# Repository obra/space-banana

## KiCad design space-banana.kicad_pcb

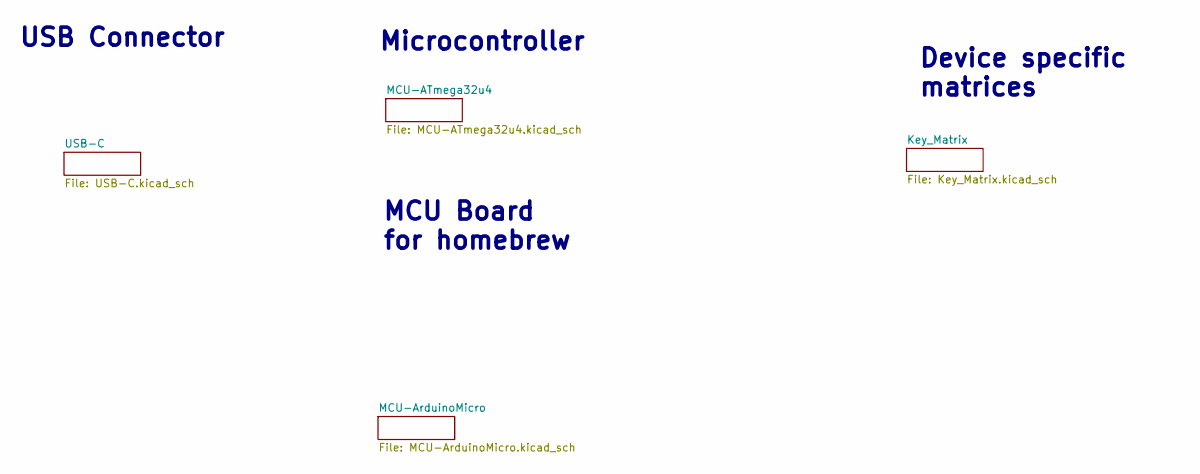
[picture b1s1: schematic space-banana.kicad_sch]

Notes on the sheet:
Microcontroller
Device specific matrices
MCU Board for homebrew
USB Connector

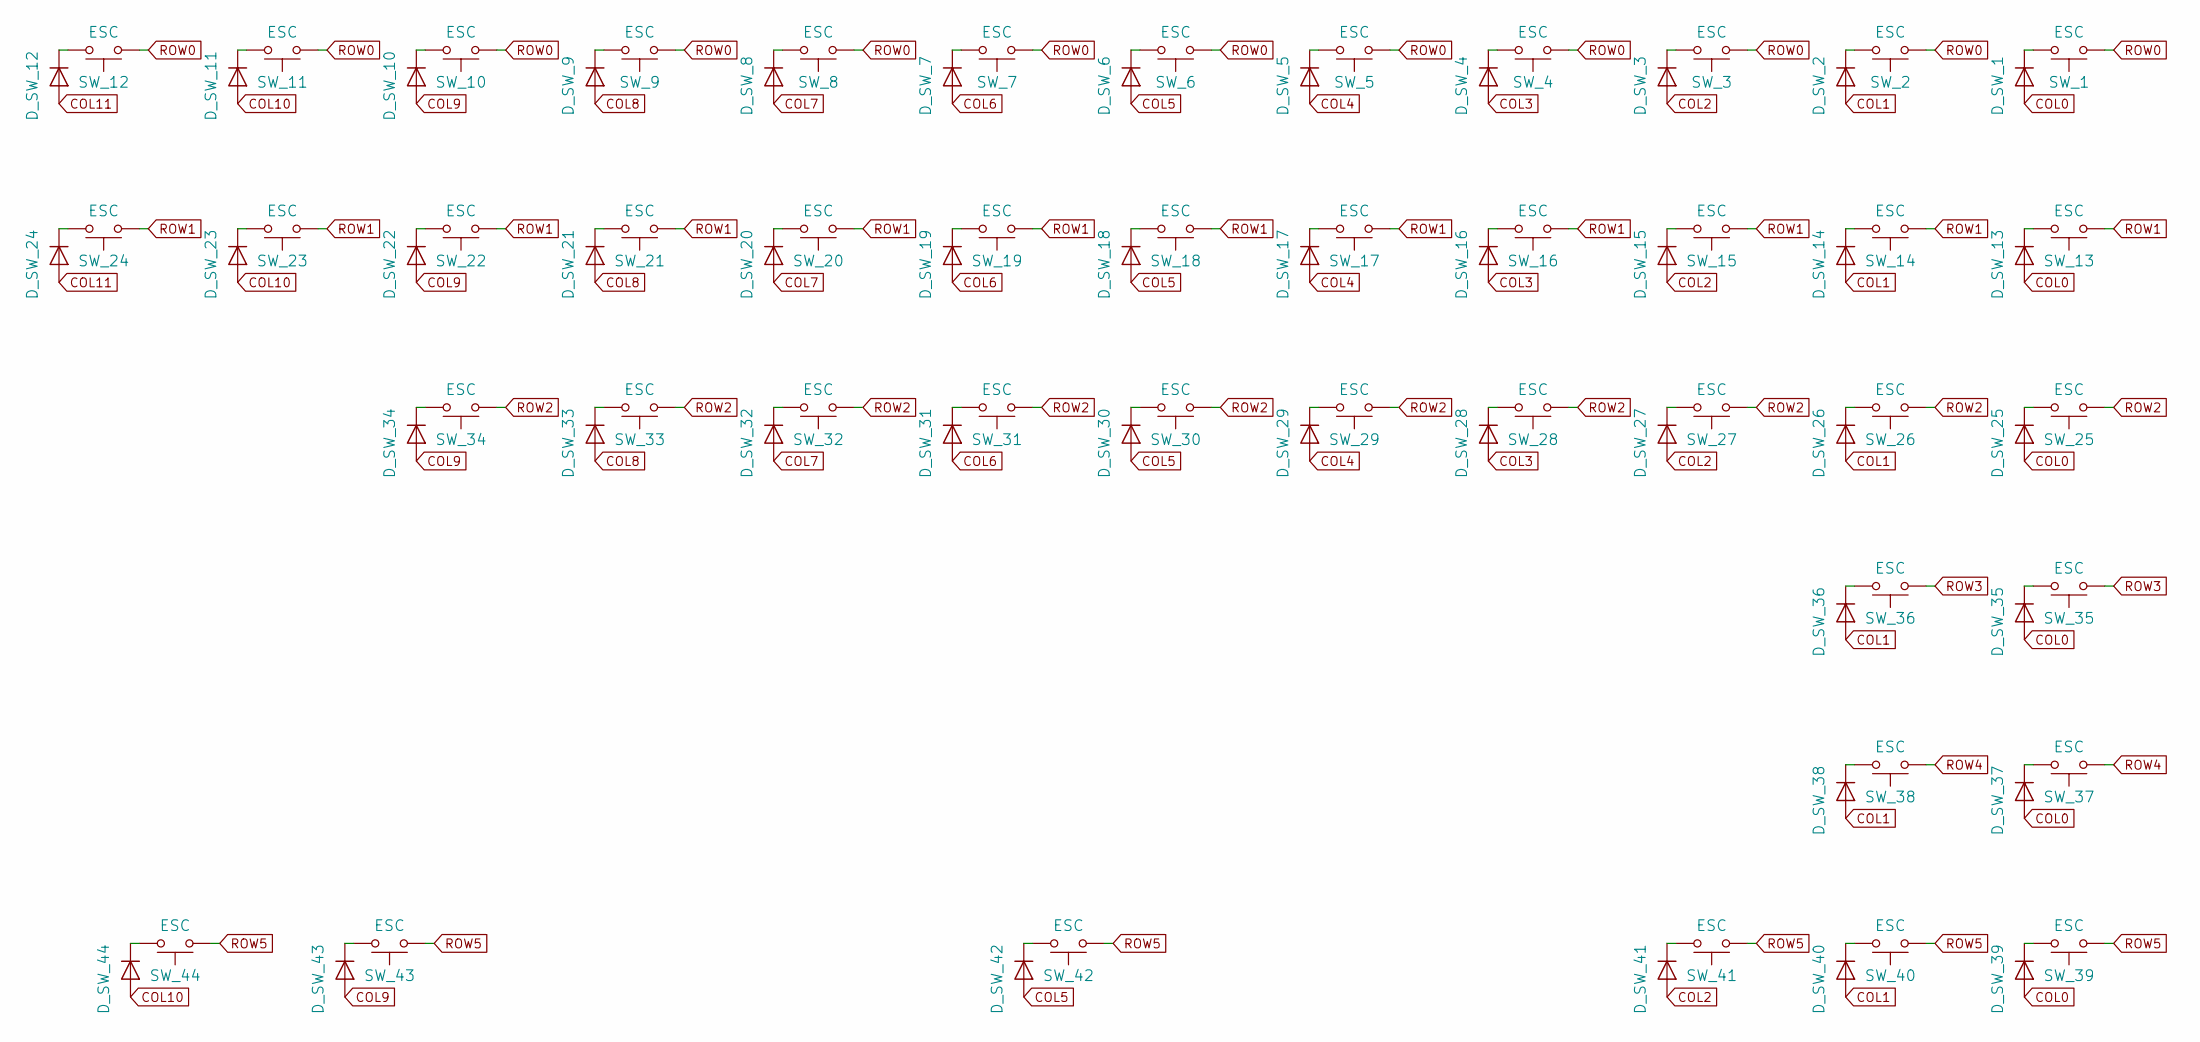
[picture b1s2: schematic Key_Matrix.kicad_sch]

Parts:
D_SW_1, D_SW_2, D_SW_3, D_SW_4, D_SW_5, D_SW_6, D_SW_7, D_SW_8, D_SW_9, D_SW_10, D_SW_11, D_SW_12, D_SW_13, D_SW_14, D_SW_15, D_SW_16, D_SW_17, D_SW_18, D_SW_19, D_SW_20, D_SW_21, D_SW_22, D_SW_23, D_SW_24, D_SW_25, D_SW_26, D_SW_27, D_SW_28, D_SW_29, D_SW_30, D_SW_31, D_SW_32, D_SW_33, D_SW_34, D_SW_35, D_SW_36, D_SW_37, D_SW_38, D_SW_39, D_SW_40, D_SW_41, D_SW_42, D_SW_43, D_SW_44: D_SOD-123
SW_1, SW_2, SW_3, SW_4, SW_5, SW_6, SW_7, SW_8, SW_9, SW_10, SW_11, SW_12, SW_13, SW_14, SW_15, SW_16, SW_17, SW_18, SW_19, SW_20, SW_21, SW_22, SW_23, SW_24, SW_25, SW_26, SW_27, SW_28, SW_29, SW_30, SW_31, SW_32, SW_33, SW_34, SW_35, SW_36, SW_37, SW_38, SW_39, SW_40, SW_41, SW_42, SW_43, SW_44: ESC; MX-KailhClip-1.00u-no-top-ring

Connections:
COL0: D_SW_1.2 (A), D_SW_13.2 (A), D_SW_25.2 (A), D_SW_35.2 (A), D_SW_37.2 (A), D_SW_39.2 (A); also elsewhere on the board
COL1: D_SW_2.2 (A), D_SW_14.2 (A), D_SW_26.2 (A), D_SW_36.2 (A), D_SW_38.2 (A), D_SW_40.2 (A); also elsewhere on the board
COL2: D_SW_3.2 (A), D_SW_15.2 (A), D_SW_27.2 (A), D_SW_41.2 (A); also elsewhere on the board
COL3: D_SW_4.2 (A), D_SW_16.2 (A), D_SW_28.2 (A); also elsewhere on the board
COL4: D_SW_5.2 (A), D_SW_17.2 (A), D_SW_29.2 (A); also elsewhere on the board
COL5: D_SW_6.2 (A), D_SW_18.2 (A), D_SW_30.2 (A), D_SW_42.2 (A); also elsewhere on the board
COL6: D_SW_7.2 (A), D_SW_19.2 (A), D_SW_31.2 (A); also elsewhere on the board
COL7: D_SW_8.2 (A), D_SW_20.2 (A), D_SW_32.2 (A); also elsewhere on the board
COL8: D_SW_9.2 (A), D_SW_21.2 (A), D_SW_33.2 (A); also elsewhere on the board
COL9: D_SW_10.2 (A), D_SW_22.2 (A), D_SW_34.2 (A), D_SW_43.2 (A); also elsewhere on the board
COL10: D_SW_11.2 (A), D_SW_23.2 (A), D_SW_44.2 (A); also elsewhere on the board
COL11: D_SW_12.2 (A), D_SW_24.2 (A); also elsewhere on the board
unnamed: D_SW_1.1 (K), SW_1.2
unnamed: D_SW_2.1 (K), SW_2.2
unnamed: D_SW_3.1 (K), SW_3.2
unnamed: D_SW_4.1 (K), SW_4.2
unnamed: D_SW_5.1 (K), SW_5.2
unnamed: D_SW_6.1 (K), SW_6.2
unnamed: D_SW_7.1 (K), SW_7.2
unnamed: D_SW_8.1 (K), SW_8.2
unnamed: D_SW_9.1 (K), SW_9.2
unnamed: D_SW_10.1 (K), SW_10.2
unnamed: D_SW_11.1 (K), SW_11.2
unnamed: D_SW_12.1 (K), SW_12.2
unnamed: D_SW_13.1 (K), SW_13.2
unnamed: D_SW_14.1 (K), SW_14.2
unnamed: D_SW_15.1 (K), SW_15.2
unnamed: D_SW_16.1 (K), SW_16.2
unnamed: D_SW_17.1 (K), SW_17.2
unnamed: D_SW_18.1 (K), SW_18.2
unnamed: D_SW_19.1 (K), SW_19.2
unnamed: D_SW_20.1 (K), SW_20.2
unnamed: D_SW_21.1 (K), SW_21.2
unnamed: D_SW_22.1 (K), SW_22.2
unnamed: D_SW_23.1 (K), SW_23.2
unnamed: D_SW_24.1 (K), SW_24.2
unnamed: D_SW_25.1 (K), SW_25.2
unnamed: D_SW_26.1 (K), SW_26.2
unnamed: D_SW_27.1 (K), SW_27.2
unnamed: D_SW_28.1 (K), SW_28.2
unnamed: D_SW_29.1 (K), SW_29.2
unnamed: D_SW_30.1 (K), SW_30.2
unnamed: D_SW_31.1 (K), SW_31.2
unnamed: D_SW_32.1 (K), SW_32.2
unnamed: D_SW_33.1 (K), SW_33.2
unnamed: D_SW_34.1 (K), SW_34.2
unnamed: D_SW_35.1 (K), SW_35.2
unnamed: D_SW_36.1 (K), SW_36.2
unnamed: D_SW_37.1 (K), SW_37.2
unnamed: D_SW_38.1 (K), SW_38.2
unnamed: D_SW_39.1 (K), SW_39.2
unnamed: D_SW_40.1 (K), SW_40.2
unnamed: D_SW_41.1 (K), SW_41.2
unnamed: D_SW_42.1 (K), SW_42.2
unnamed: D_SW_43.1 (K), SW_43.2
unnamed: D_SW_44.1 (K), SW_44.2
ROW0: SW_1.1, SW_2.1, SW_3.1, SW_4.1, SW_5.1, SW_6.1, SW_7.1, SW_8.1, SW_9.1, SW_10.1, SW_11.1, SW_12.1; also elsewhere on the board
ROW1: SW_13.1, SW_14.1, SW_15.1, SW_16.1, SW_17.1, SW_18.1, SW_19.1, SW_20.1, SW_21.1, SW_22.1, SW_23.1, SW_24.1; also elsewhere on the board
ROW2: SW_25.1, SW_26.1, SW_27.1, SW_28.1, SW_29.1, SW_30.1, SW_31.1, SW_32.1, SW_33.1, SW_34.1; also elsewhere on the board
ROW3: SW_35.1, SW_36.1; also elsewhere on the board
ROW4: SW_37.1, SW_38.1; also elsewhere on the board
ROW5: SW_39.1, SW_40.1, SW_41.1, SW_42.1, SW_43.1, SW_44.1

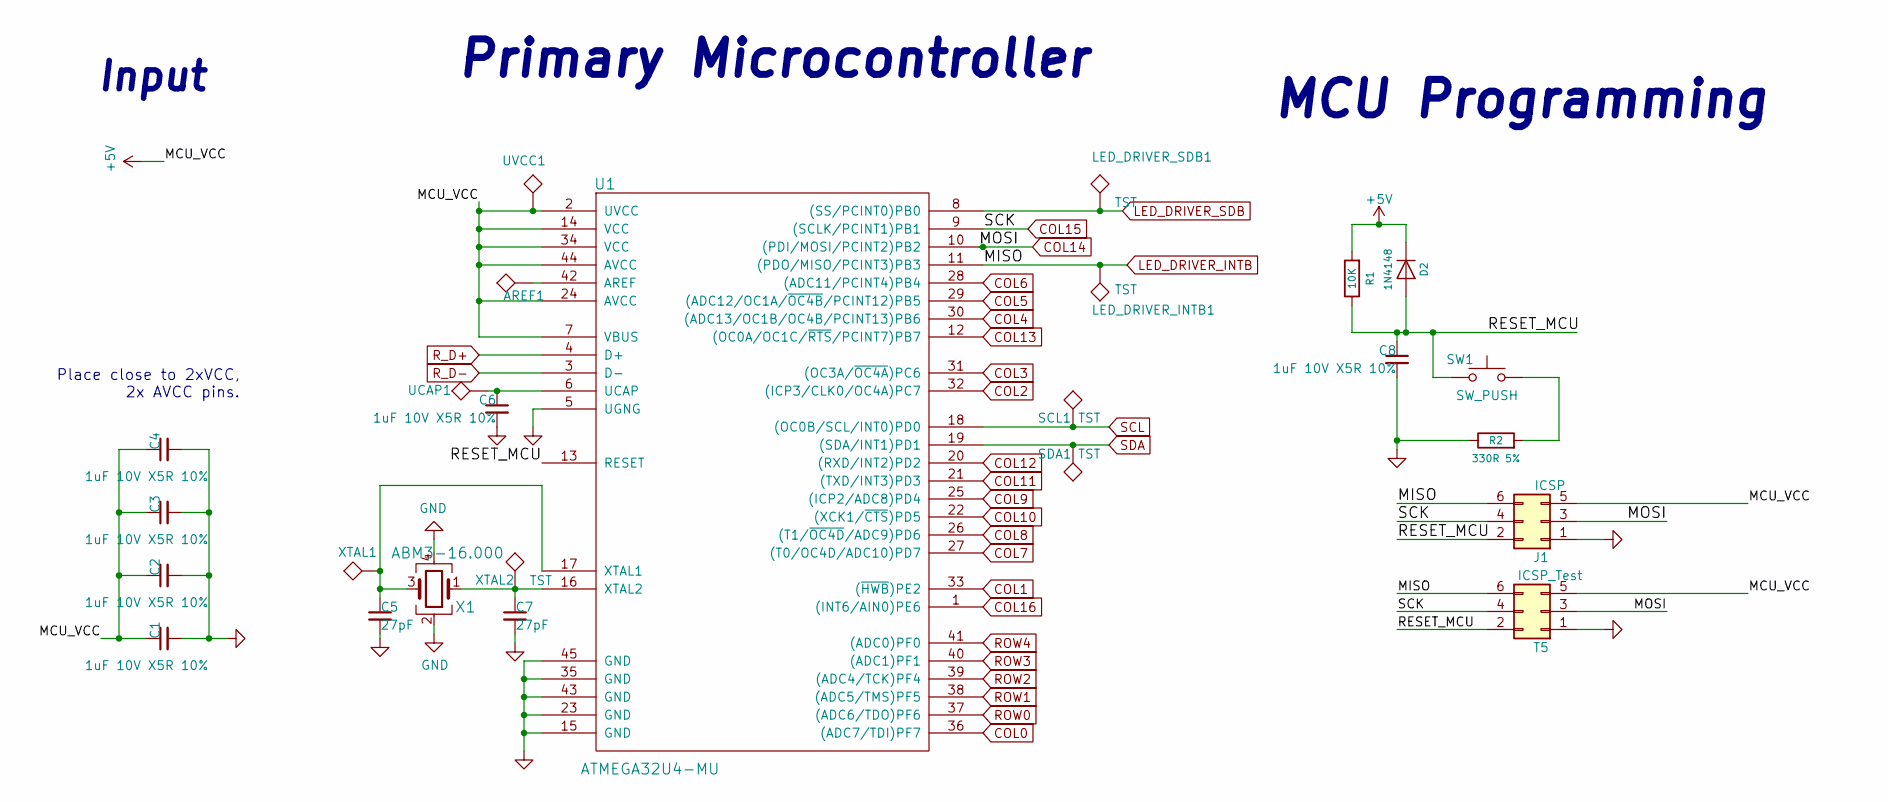
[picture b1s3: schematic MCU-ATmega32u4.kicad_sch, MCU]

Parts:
AREF1: TST; TestPoint_Pad_D1.5mm
C1, C2, C3, C4, C6, C8: 1uF 10V X5R 10%; C_0603_1608Metric; MPN CC0603KRX5R6BB105; DigiKey 311-1443-2-ND
C5, C7: 27pF; C_0603_1608Metric; MPN CC0603JRNPO9BN270; DigiKey 311-1063-1-ND
D2: 1N4148; D_SOD-123; MPN 1N4148W-7-F; DigiKey 1N4148W-FDITR-ND
J1: ICSP; Model_01_ICSP_cutout_pins; MPN M20-8760342; DigiKey 952-1922-ND
LED_DRIVER_INTB1: TST; TestPoint_Pad_D1.5mm
LED_DRIVER_SDB1: TST; TestPoint_Pad_D1.5mm
R1: 10K; R_0603_1608Metric; MPN RR0816P-103-D; DigiKey RR08P10.0KDTR-ND
R2: 330R 5%; R_0603_1608Metric; MPN 311-330GRTR-ND; DigiKey 311-330GRTR-ND
SCL1: TST; TestPoint_Pad_D1.5mm
SDA1: TST; TestPoint_Pad_D1.5mm
SW1: SW_PUSH; SW_SPST_TL3342; MPN TL3342F160QG/TR; DigiKey EG2531TR-ND
T5: ICSP_Test; Six_Pin_Test_Point
U1: ATMEGA32U4-MU; TQFP-44_10x10mm_Pitch0.8mm-Plus-QFN_44_7x7mm_Pitch_0.5mm; MPN ATMEGA32U4-MU; DigiKey ATMEGA32U4-MU-ND
UCAP1: TST; TestPoint_Pad_D1.5mm
UVCC1: TST; TestPoint_Pad_D1.5mm
X1: ABM3-16.000; ABM3_Crystal_Oscillator; MPN X1E000021069600; DigiKey TSX-322516.0000MF20G-C-ND
XTAL1, XTAL2: TST; TestPoint_Pad_D1.5mm

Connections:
+5V: C1.1, C2.1, C3.1, C4.1, D2.1 (K), J1.5, R1.2, T5.5, U1.2 (UVCC), U1.7 (VBUS), U1.14 (VCC), U1.24 (AVCC), U1.34 (VCC), U1.44 (AVCC), UVCC1.1; also elsewhere on the board
/MCU-ATmega32u4/RESET_MCU: C8.1, D2.2 (A), J1.2, R1.1, SW1.2, T5.2, U1.13 (RESET)
COL0: U1.36 ((ADC7/TDI)PF7); also elsewhere on the board
COL1: U1.33 ((~HWB)PE2); also elsewhere on the board
COL2: U1.32 ((ICP3/CLK0/OC4A)PC7); also elsewhere on the board
COL3: U1.31 ((OC3A/~OC4A)PC6); also elsewhere on the board
COL4: U1.30 ((ADC13/OC1B/OC4B/PCINT13)PB6); also elsewhere on the board
COL5: U1.29 ((ADC12/OC1A/~OC4B/PCINT12)PB5); also elsewhere on the board
COL6: U1.28 ((ADC11/PCINT4)PB4); also elsewhere on the board
COL7: U1.27 ((T0/OC4D/ADC10)PD7); also elsewhere on the board
COL8: U1.26 ((T1/~OC4D/ADC9)PD6); also elsewhere on the board
COL9: U1.25 ((ICP2/ADC8)PD4); also elsewhere on the board
COL10: U1.22 ((XCK1/~CTS)PD5); also elsewhere on the board
COL11: U1.21 ((TXD/INT3)PD3); also elsewhere on the board
COL12: U1.20 ((RXD/INT2)PD2); also elsewhere on the board
COL13: U1.12 ((OC0A/OC1C/~RTS/PCINT7)PB7); also elsewhere on the board
COL14: J1.3, T5.3, U1.10 ((PDI/MOSI/PCINT2)PB2); also elsewhere on the board
COL15: J1.4, T5.4, U1.9 ((SCLK/PCINT1)PB1); also elsewhere on the board
COL16: U1.1 ((INT6/AIN0)PE6)
LED_DRIVER_INTB: J1.6, LED_DRIVER_INTB1.1, T5.6, U1.11 ((PDO/MISO/PCINT3)PB3)
LED_DRIVER_SDB: LED_DRIVER_SDB1.1, U1.8 ((SS/PCINT0)PB0)
unnamed: AREF1.1, U1.42 (AREF)
unnamed: C5.1, U1.17 (XTAL1), X1.3, XTAL1.1
unnamed: C6.1, U1.6 (UCAP), UCAP1.1
unnamed: C7.1, U1.16 (XTAL2), X1.1, XTAL2.1
unnamed: R2.2, SW1.1
ROW0: U1.37 ((ADC6/TDO)PF6); also elsewhere on the board
ROW1: U1.38 ((ADC5/TMS)PF5); also elsewhere on the board
ROW2: U1.39 ((ADC4/TCK)PF4); also elsewhere on the board
ROW3: U1.40 ((ADC1)PF1); also elsewhere on the board
ROW4: U1.41 ((ADC0)PF0); also elsewhere on the board
R_D+: U1.4 (D+); also elsewhere on the board
R_D-: U1.3 (D-); also elsewhere on the board
SCL: SCL1.1, U1.18 ((OC0B/SCL/INT0)PD0)
SDA: SDA1.1, U1.19 ((SDA/INT1)PD1)

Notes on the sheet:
Primary Microcontroller
Input
Place close to 2xVCC, 2x AVCC pins.
MCU Programming

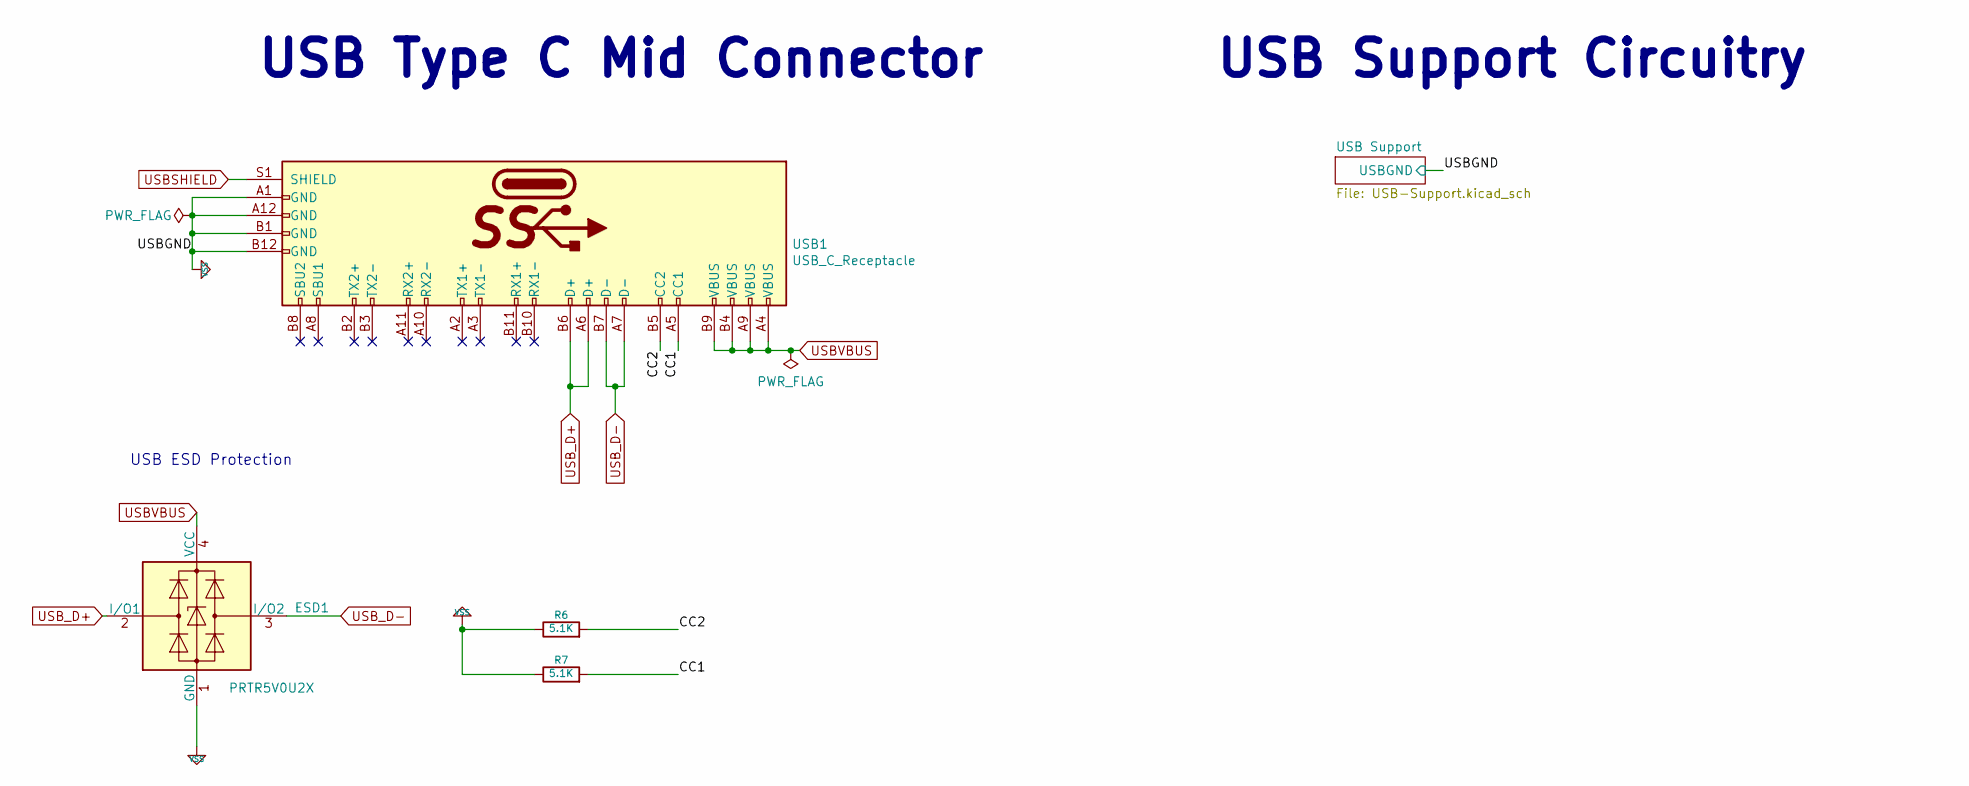
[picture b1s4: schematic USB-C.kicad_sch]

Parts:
ESD1: PRTR5V0U2X; MPN PRTR5V0U2X; DigiKey 1727-3884-2-ND
R6: 5.1K; R_0603_1608Metric; MPN RR0816P-512-D; DigiKey RR08P5.1KDTR-ND
R7: 5.1K; R_0603_1608Metric; MPN RT0603BRD075K1L; DigiKey YAG1696TR-ND
USB1: USB_C_Receptacle; USB-TYPE-C-MIDMOUNT; MPN DX07B024JJ2R1500

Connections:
/USB-C/CC1: R7.2, USB1.A5 (CC1)
/USB-C/CC2: R6.2, USB1.B5 (CC2)
USBSHIELD: USB1.S1 (SHIELD); also elsewhere on the board
USBVBUS: ESD1.4 (VCC), USB1.A4 (VBUS), USB1.A9 (VBUS), USB1.B4 (VBUS), USB1.B9 (VBUS); also elsewhere on the board
USB_D+: ESD1.2 (I/O1), USB1.A6 (D+), USB1.B6 (D+); also elsewhere on the board
USB_D-: ESD1.3 (I/O2), USB1.A7 (D-), USB1.B7 (D-); also elsewhere on the board

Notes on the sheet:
USB ESD Protection
USB Type C Mid Connector
USB Support Circuitry

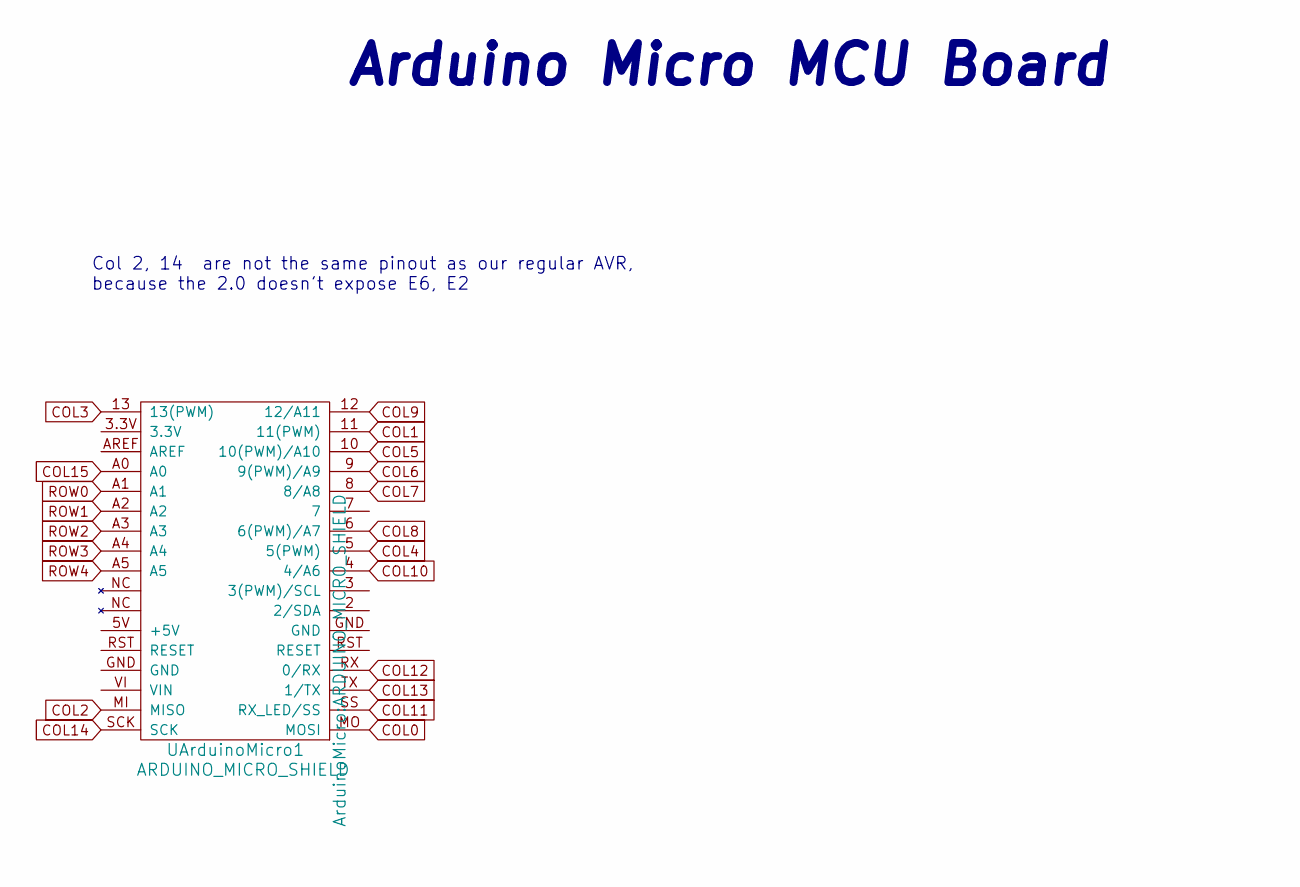
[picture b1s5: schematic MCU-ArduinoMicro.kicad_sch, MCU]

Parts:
UArduinoMicro1: ARDUINO_MICRO_SHIELD

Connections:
COL0: UArduinoMicro1.MO (MOSI); also elsewhere on the board
COL1: UArduinoMicro1.11 (11(PWM)); also elsewhere on the board
COL2: UArduinoMicro1.MI (MISO); also elsewhere on the board
COL3: UArduinoMicro1.13 (13(PWM)); also elsewhere on the board
COL4: UArduinoMicro1.5 (5(PWM)); also elsewhere on the board
COL5: UArduinoMicro1.10 (10(PWM)/A10); also elsewhere on the board
COL6: UArduinoMicro1.9 (9(PWM)/A9); also elsewhere on the board
COL7: UArduinoMicro1.8 (8/A8); also elsewhere on the board
COL8: UArduinoMicro1.6 (6(PWM)/A7); also elsewhere on the board
COL9: UArduinoMicro1.12 (12/A11); also elsewhere on the board
COL10: UArduinoMicro1.4 (4/A6); also elsewhere on the board
COL11: UArduinoMicro1.SS (RX_LED/SS); also elsewhere on the board
COL12: UArduinoMicro1.RX (0/RX); also elsewhere on the board
COL13: UArduinoMicro1.TX (1/TX); also elsewhere on the board
COL14: UArduinoMicro1.SCK; also elsewhere on the board
COL15: UArduinoMicro1.A0; also elsewhere on the board
ROW0: UArduinoMicro1.A1; also elsewhere on the board
ROW1: UArduinoMicro1.A2; also elsewhere on the board
ROW2: UArduinoMicro1.A3; also elsewhere on the board
ROW3: UArduinoMicro1.A4; also elsewhere on the board
ROW4: UArduinoMicro1.A5; also elsewhere on the board

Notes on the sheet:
Col 2, 14 are not the same pinout as our regular AVR, because the 2.0 doesn't expose E6, E2
Arduino Micro MCU Board

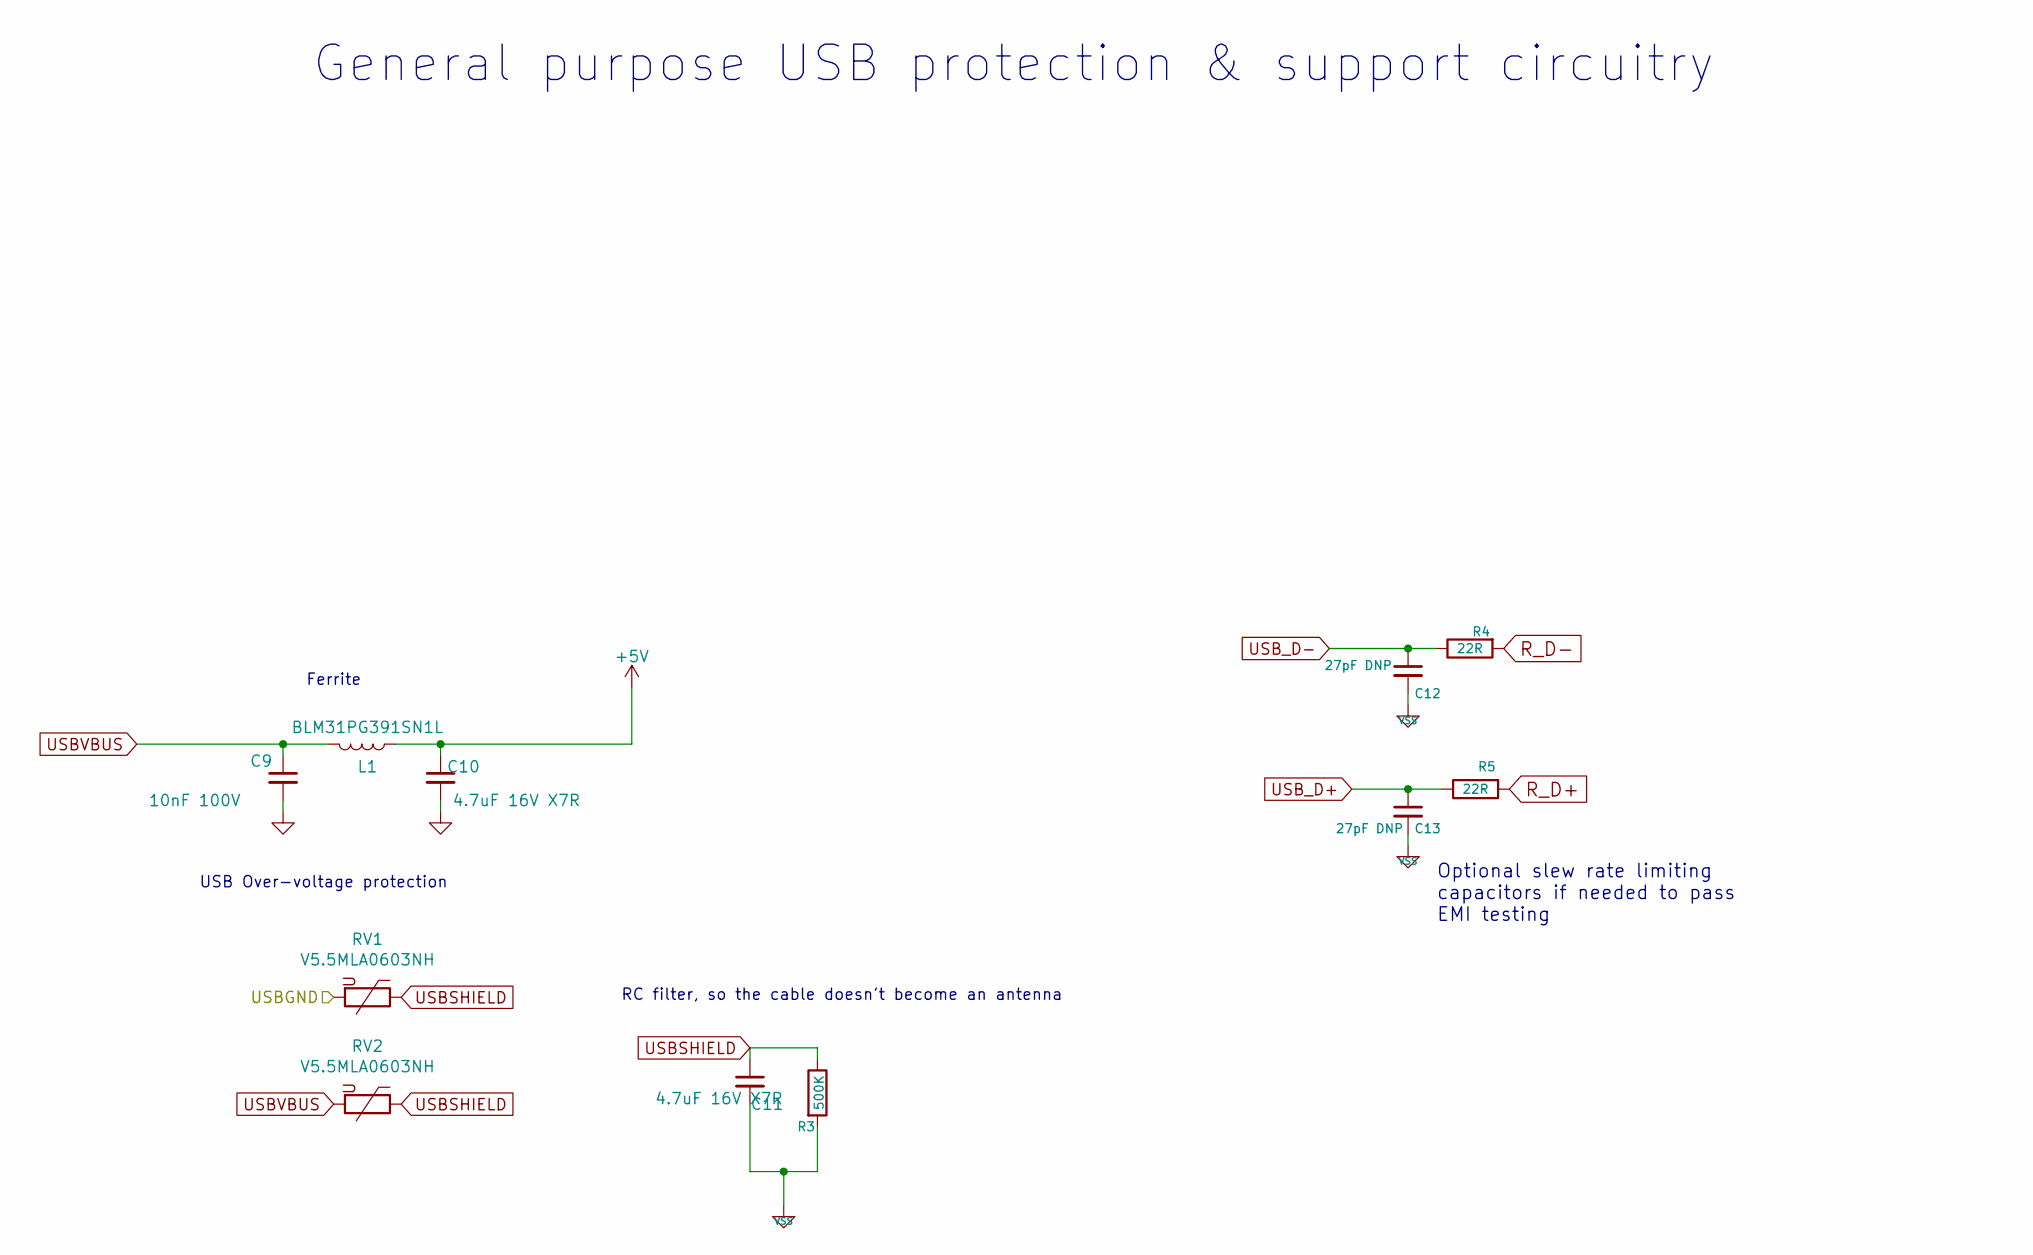
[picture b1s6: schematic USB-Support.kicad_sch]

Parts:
C9: 10nF 100V; C_0805_2012Metric; MPN CC0805KKX7R7BB475; DigiKey 311-1883-2-ND
C10: 4.7uF 16V X7R; C_0805_2012Metric; MPN CC0805KKX7R7BB475; DigiKey 311-1883-2-ND
C11: 4.7uF 16V X7R; C_0805_2012Metric; MPN CC0805KRX7R0BB103; DigiKey 311-1475-1-ND
C12, C13: 27pF DNP; C_0603_1608Metric; MPN CC0603JRNPO9BN270; DigiKey 311-1063-1-ND
L1: BLM31PG391SN1L; R_1206_3216Metric; MPN BLM31PG391SN1L; DigiKey 490-5229-2-ND
R3: 500K; R_0603_1608Metric; MPN RC0603FR-07499KL; DigiKey 311-499KHRTR-ND
R4, R5: 22R; R_0603_1608Metric; MPN RC0603FR-0722RL; DigiKey 311-22.0HRTR-ND
RV1, RV2: V5.5MLA0603NH; R_0603_1608Metric; MPN V5.5MLA0603NH; DigiKey F3363CT-ND

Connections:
+5V: C10.1, L1.1; also elsewhere on the board
R_D+: R5.2; also elsewhere on the board
R_D-: R4.2; also elsewhere on the board
USBSHIELD: C11.1, R3.1, RV1.1, RV2.1; also elsewhere on the board
USBVBUS: C9.1, L1.2, RV2.2; also elsewhere on the board
USB_D+: C13.1, R5.1; also elsewhere on the board
USB_D-: C12.1, R4.1; also elsewhere on the board

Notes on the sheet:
USB Over-voltage protection
General purpose USB protection & support circuitry
RC filter, so the cable doesn't become an antenna
Ferrite
Optional slew rate limiting capacitors if needed to pass EMI testing

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
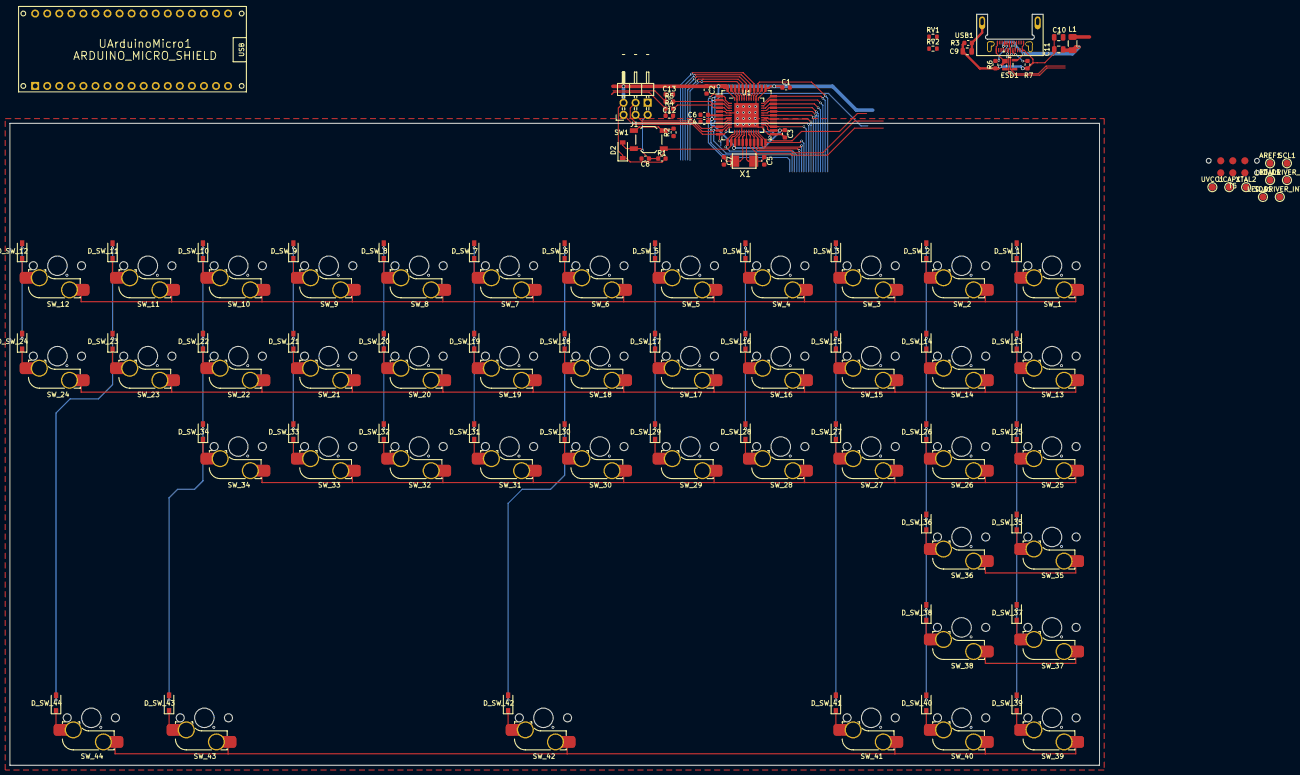
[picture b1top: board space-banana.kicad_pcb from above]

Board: 2 copper layers, 229.6 x 158.2 mm, 129 parts (0 on the bottom side), 86 nets.

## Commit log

2022-03-14 Initial commit - autogenerated by keygen and then tweaked ever so slightly to be a bit less crazy
2022-03-14 sync schematic to pcb

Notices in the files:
parts and their libraries:
Copyright 2016 Accelerated Designs. All rights reserved.
